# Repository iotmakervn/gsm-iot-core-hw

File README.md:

# Dự án GSM-IOT-CORE

## Mô tả tính năng

## Phần cứng

### Mạch nguyên lý

### Mạch PCB

### 3D
#### Top view

#### Button view

### Film

# Giấy phép

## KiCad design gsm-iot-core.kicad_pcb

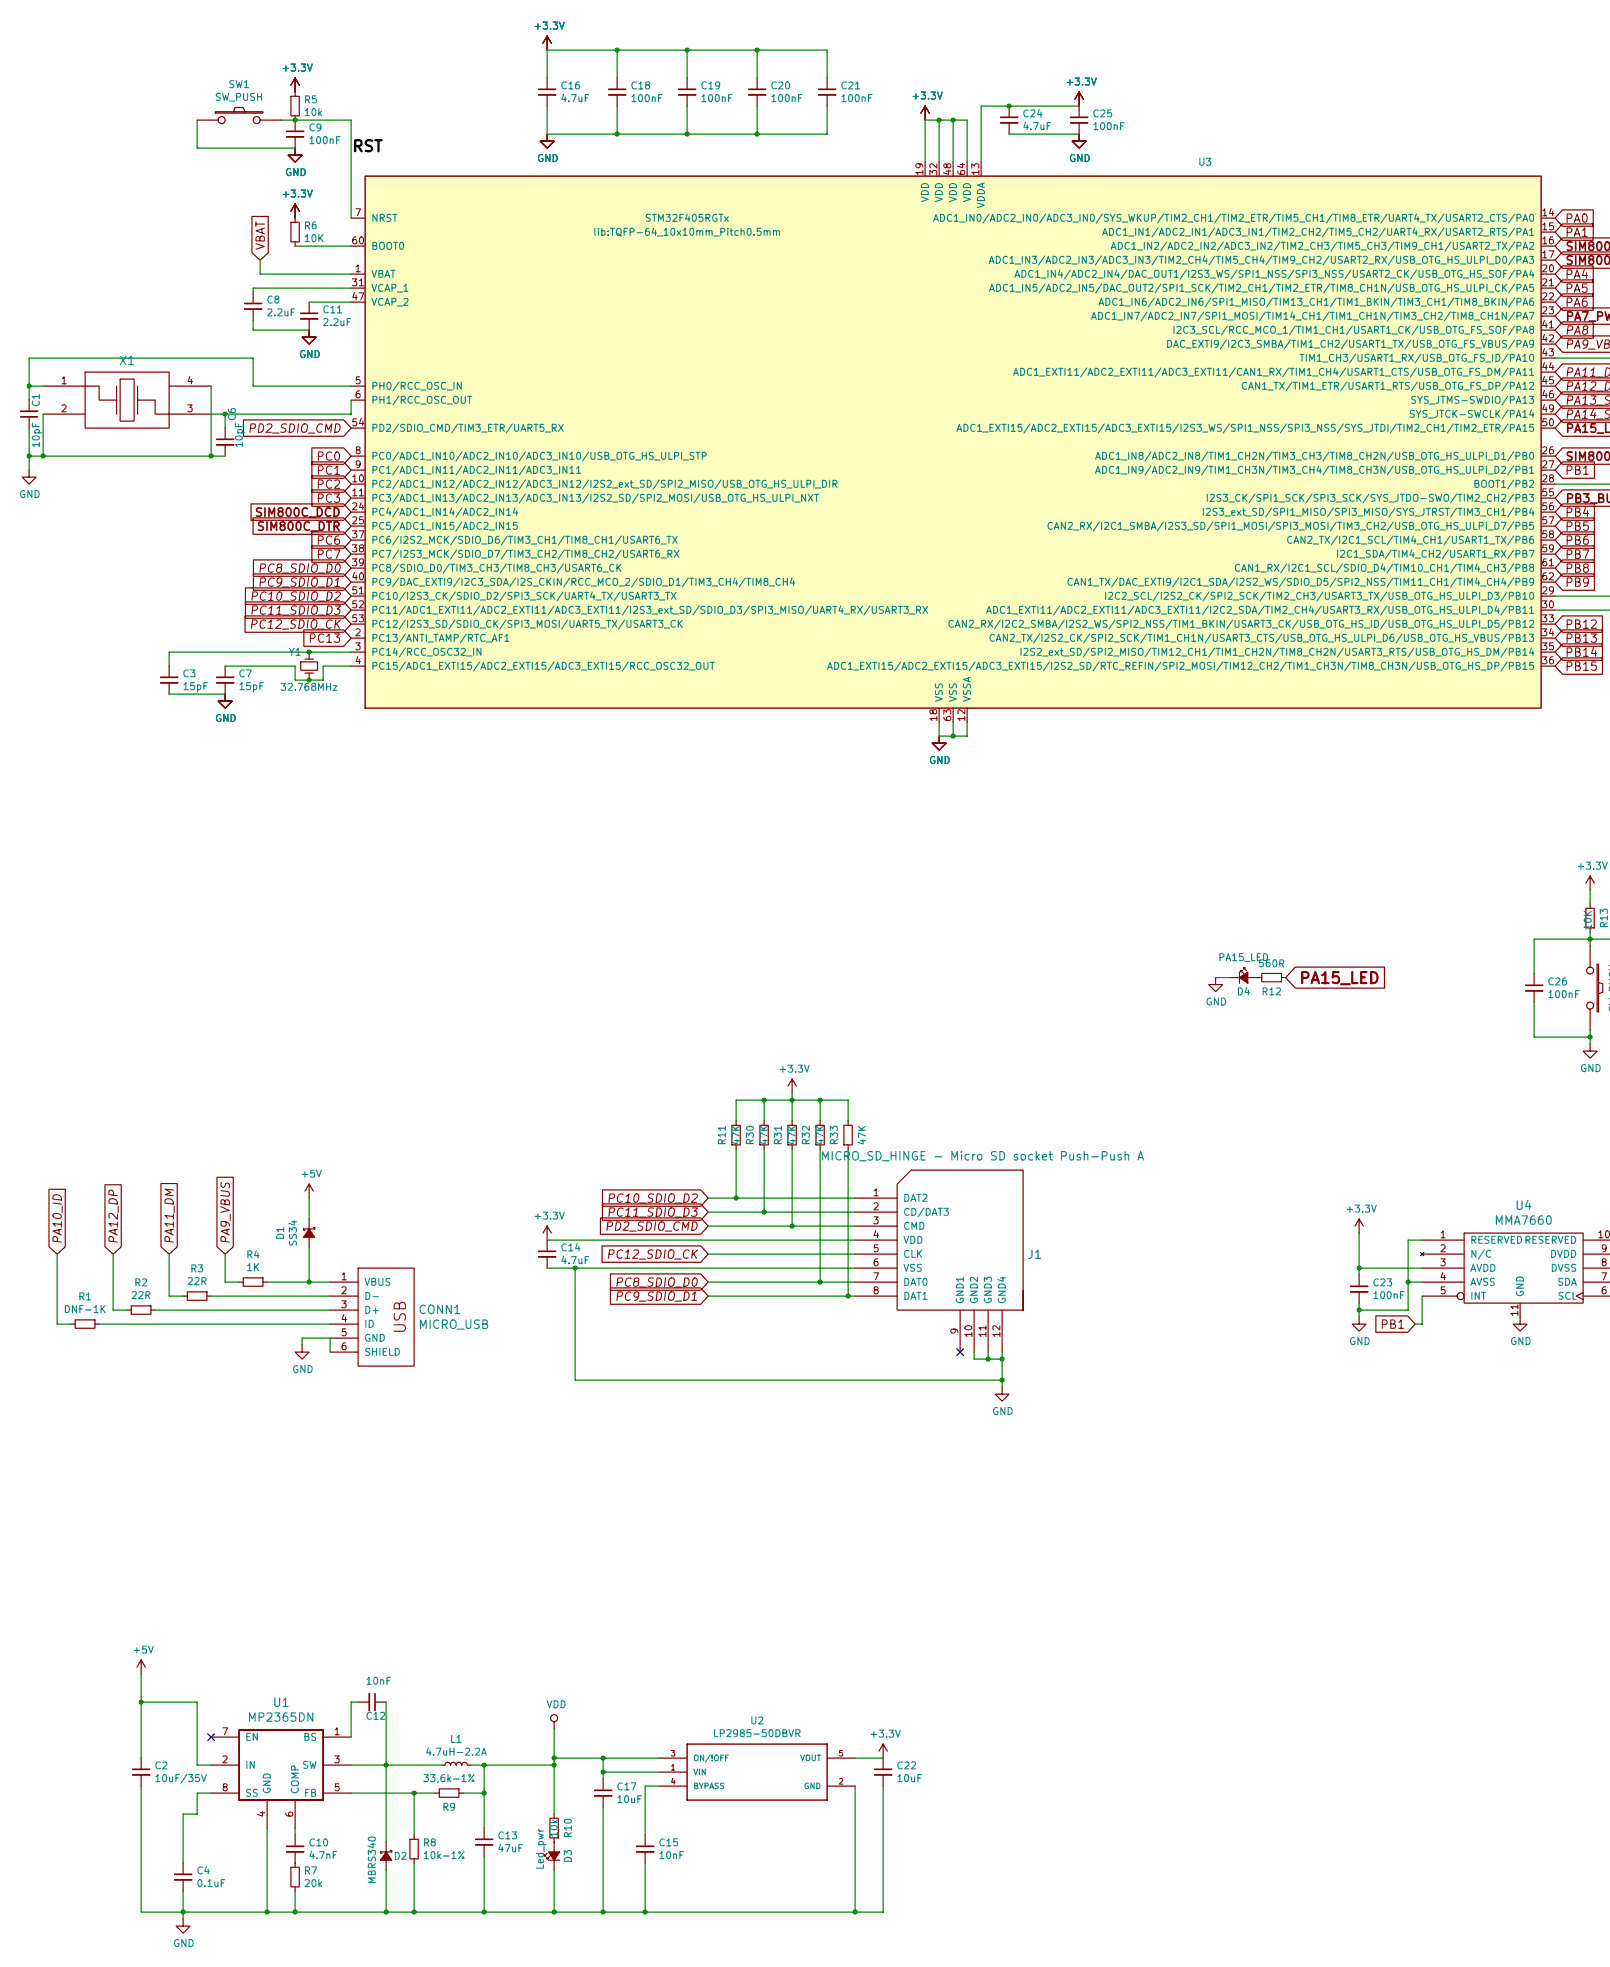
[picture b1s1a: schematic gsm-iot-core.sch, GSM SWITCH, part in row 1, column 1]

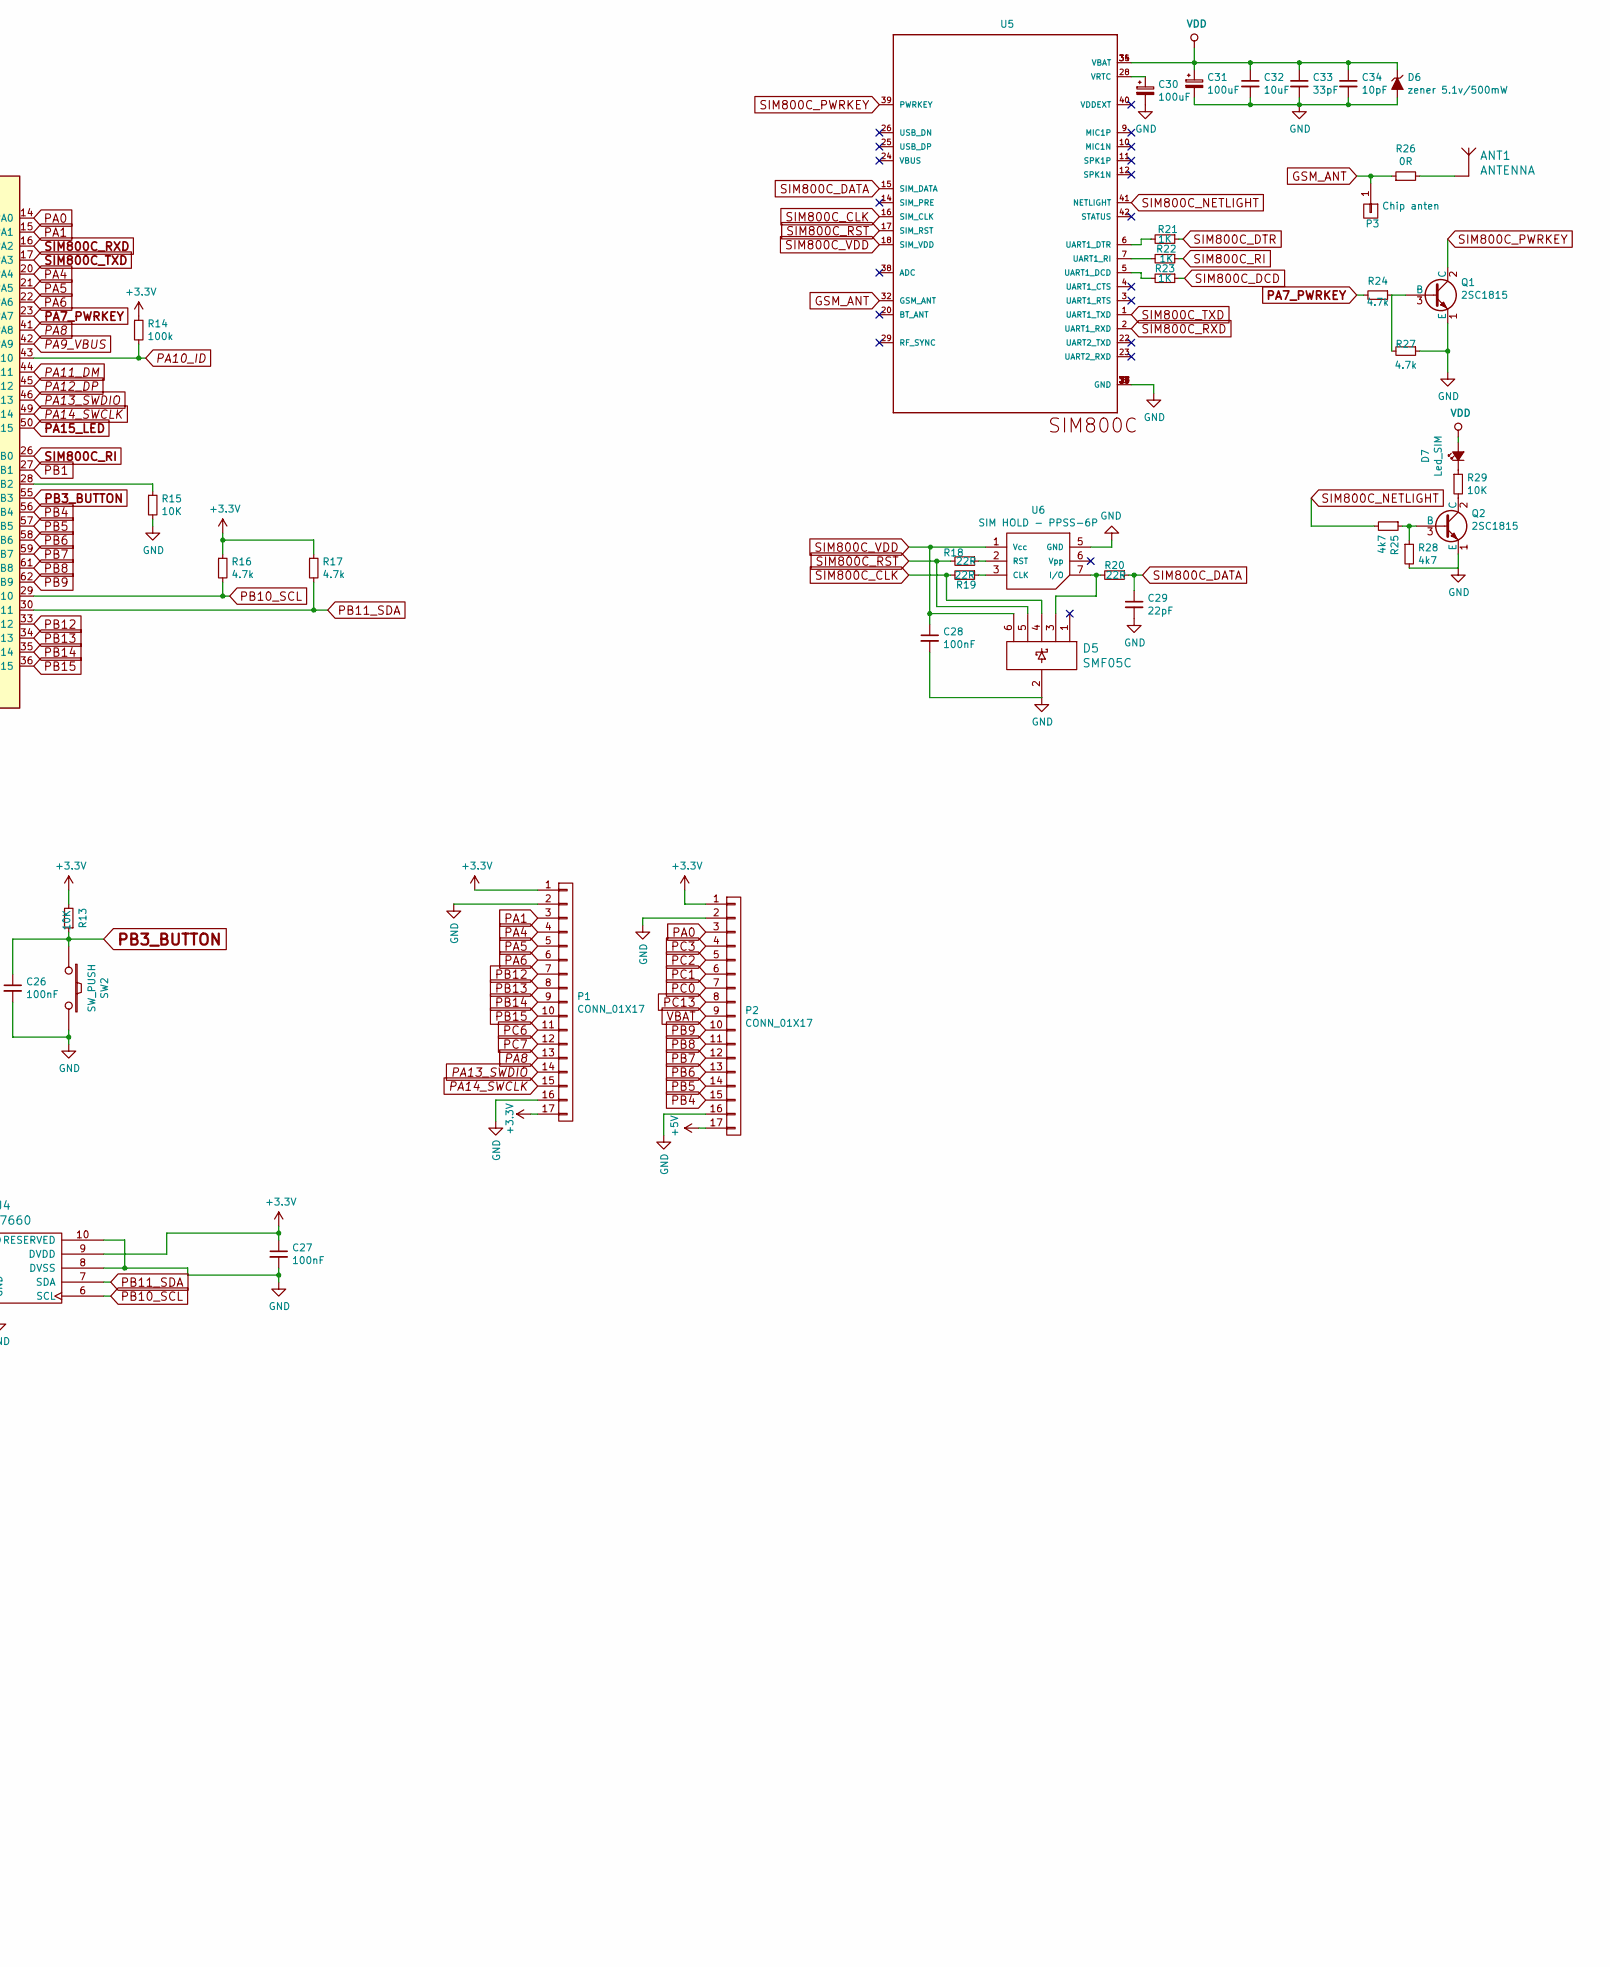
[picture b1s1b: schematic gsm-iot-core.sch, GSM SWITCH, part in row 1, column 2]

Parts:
ANT1: ANTENNA; coaxial_u.fl-r-smt-1
C1, C6, C34: 10pF; C_0603
C2: 10uF/35V; C_1210
C3, C7: 15pF; C_0603
C4: 0.1uF; C_0603
C8, C11: 2.2uF; C_0603
C9, C18, C19, C20, C21, C23, C25, C26, C27, C28: 100nF; C_0603
C10: 4.7nF; C_0603
C12, C15: 10nF; C_0603
C13: 47uF; C_0603
C14, C16, C24: 4.7uF; C_0603
C17, C22, C32: 10uF; C_0603
C29: 22pF; C_0603
C30, C31: 100uF; C_1210
C33: 33pF; C_0603
CONN1: MICRO_USB; Micro_usb_B_smd
D1: SS34; do214ac
D2: MBRS340; do214ab
D3: Led_pwr; LED_0805
D4: PA15_LED; LED_0805
D5: SMF05C; SC-70-6
D6: zener 5.1v/500mW; SOD-123
D7: Led_SIM; LED_0805
J1: MICRO_SD_HINGE - Micro SD socket Push-Push A; MicroSD_Push-Push-A
L1: 4.7uH-2.2A; Choke_SMD_6.3x6.3_H3
P1, P2: CONN_01X17; Pin_Header_Straight_1x17
P3: Chip anten; point_test
Q1, Q2: 2SC1815; SOT-23
R1: DNF-1K; R_0603
R2, R3, R18, R19, R20: 22R; R_0603
R4, R21, R22, R23: 1K; R_0603
R5, R10: 10k; R_0603
R6, R13, R15, R29: 10K; R_0603
R7: 20k; R_0603
R8: 10k-1%; R_0603
R9: 33,6k-1%; R_0603
R11, R30, R31, R32, R33: 47K; R_0603
R12: 560R; R_0603
R14: 100k; R_0603
R16, R17, R24, R27: 4.7k; R_0603
R25, R28: 4k7; R_0603
R26: 0R; R_0603
SW1, SW2: SW_PUSH; SW_SPST_B3U-1000P-B
U1: MP2365DN; SOIC-8-N
U2: LP2985-50DBVR; SOT-23-5
U3: STM32F405RGTx; TQFP-64_10x10mm_Pitch0.5mm
U4: MMA7660; DFN-10-1EP_3x3mm_Pitch0.5mm
U5: SIM800C
U6: SIM HOLD - PPSS-6P; 115I-AEAA
X1: CRYSTAL-24M; Crystal_SMD_5032_4Pads
Y1: 32.768MHz; crystal_smd_32.768_2Pin

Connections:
+3V3: C14.1, C16.1, C18.1, C19.1, C20.1, C21.1, C22.1, C23.1, C24.1, C25.1, C27.1, J1.4 (VDD), P1.1, P1.17, P2.1, R5.1, R6.1, R11.2, R13.2, R14.1, R16.1, R17.1, R30.2, R31.2, R32.2, R33.2, U2.5 (VOUT), U3.13 (VDDA), U3.19 (VDD), U3.32 (VDD), U3.48 (VDD), U3.64 (VDD), U4.3 (AVDD), U4.9 (DVDD)
+5V: C2.1, D1.1 (K), P2.17, U1.2 (IN)
/RST: C9.1, R5.2, SW1.2, U3.7 (NRST)
GND: C1.1, C2.2, C3.2, C4.2, C6.2, C7.2, C8.2, C9.2, C11.2, C13.2, C14.2, C15.2, C16.2, C17.2, C18.2, C19.2, C20.2, C21.2, C22.2, C23.2, C24.2, C25.2, C26.2, C27.2, C28.2, C29.2, C30.2, C31.2, C32.2, C33.2, C34.2, CONN1.5 (GND), CONN1.6 (SHIELD), D2.2 (A), D3.1 (K), D4.1 (K), D5.2, D6.2 (A), J1.6 (VSS), J1.10 (GND2), J1.11 (GND3), J1.12 (GND4), P1.2, P1.16, P2.2, P2.16, Q1.1 (E), Q2.1 (E), R7.2, R8.2, R15.2, R27.1, R28.2, SW1.1, SW2.2, U1.4 (GND), U2.2 (GND), U3.12 (VSSA), U3.18 (VSS), U3.63 (VSS), U4.1 (RESERVED), U4.4 (AVSS), U4.8 (DVSS), U4.10 (RESERVED), U4.11 (GND), U5.8 (GND), U5.13 (GND), U5.19 (GND), U5.21 (GND), U5.27 (GND), U5.30 (GND), U5.31 (GND), U5.33 (GND), U5.36 (GND), U5.37 (GND), U6.5 (GND), X1.2, X1.4
GSM_ANT: P3.1, R26.1, U5.32 (GSM_ANT)
unnamed: ANT1.1, R26.2
unnamed: C1.2, U3.5 (PH0/RCC_OSC_IN), X1.1
unnamed: C3.1, U3.3 (PC14/RCC_OSC32_IN), Y1.1
unnamed: C4.1, U1.8 (SS)
unnamed: C6.1, U3.6 (PH1/RCC_OSC_OUT), X1.3
unnamed: C7.1, U3.4 (PC15/ADC1_EXTI15/ADC2_EXTI15/ADC3_EXTI1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), Y1.2
unnamed: C8.1, U3.31 (VCAP_1)
unnamed: C10.1, U1.6 (COMP)
unnamed: C10.2, R7.1
unnamed: C11.1, U3.47 (VCAP_2)
unnamed: C12.1, D2.1 (K), L1.1, U1.3 (SW)
unnamed: C12.2, U1.1 (BS)
unnamed: C15.1, U2.4 (BYPASS)
unnamed: C28.1, D5.6
unnamed: C30.1, U5.28 (VRTC)
unnamed: CONN1.1 (VBUS), D1.2 (A), R4.1
unnamed: CONN1.2 (D-), R3.1
unnamed: CONN1.3 (D+), R2.1
unnamed: CONN1.4 (ID), R1.1
unnamed: D3.2 (A), R10.1
unnamed: D4.2 (A), R12.2
unnamed: D5.3, R20.2, U6.7 (I/O)
unnamed: D7.1 (K), R29.1
unnamed: Q1.3 (B), R24.1, R27.2
unnamed: Q2.2 (C), R29.2
unnamed: Q2.3 (B), R25.1, R28.1
unnamed: R6.2, U3.60 (BOOT0)
unnamed: R8.1, R9.2, U1.5 (FB)
unnamed: R15.1, U3.28 (BOOT1/PB2)
unnamed: R18.1, U6.2 (RST)
unnamed: R19.1, U6.3 (CLK)
unnamed: R21.2, U5.6 (UART1_DTR)
unnamed: R22.2, U5.7 (UART1_RI)
unnamed: R23.2, U5.5 (UART1_DCD)
PA0: P2.3, U3.14 (ADC1_IN0/ADC2_IN0/ADC3_IN0/SYS_WKUP/TIM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)
PA1: P1.3, U3.15 (ADC1_IN1/ADC2_IN1/ADC3_IN1/TIM2_CH2/TIM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)
PA4: P1.4, U3.20 (ADC1_IN4/ADC2_IN4/DAC_OUT1/I2S3_WS/SPI1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)
PA5: P1.5, U3.21 (ADC1_IN5/ADC2_IN5/DAC_OUT2/SPI1_SCK/TIM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)
PA6: P1.6, U3.22 (ADC1_IN6/ADC2_IN6/SPI1_MISO/TIM13_CH1/T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)
PA7_PWRKEY: R24.2, U3.23 (ADC1_IN7/ADC2_IN7/SPI1_MOSI/TIM14_CH1/T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)
PA8: P1.13, U3.41 (I2C3_SCL/RCC_MCO_1/TIM1_CH1/USART1_CK/U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)
PA9_VBUS: R4.2, U3.42 (DAC_EXTI9/I2C3_SMBA/TIM1_CH2/USART1_TX/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)
PA10_ID: R1.2, R14.2, U3.43 (TIM1_CH3/USART1_RX/USB_OTG_FS_ID/PA10)
PA11_DM: R3.2, U3.44 (ADC1_EXTI11/ADC2_EXTI11/ADC3_EXTI11/CAN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)
PA12_DP: R2.2, U3.45 (CAN1_TX/TIM1_ETR/USART1_RTS/USB_OTG_FS_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)
PA13_SWDIO: P1.14, U3.46 (SYS_JTMS-SWDIO/PA13)
PA14_SWCLK: P1.15, U3.49 (SYS_JTCK-SWCLK/PA14)
PA15_LED: R12.1, U3.50 (ADC1_EXTI15/ADC2_EXTI15/ADC3_EXTI15/I2S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)
PB1: U3.27 (ADC1_IN9/ADC2_IN9/TIM1_CH3N/TIM3_CH4/TI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), U4.5 (INT)
PB3_BUTTON: C26.1, R13.1, SW2.1, U3.55 (I2S3_CK/SPI1_SCK/SPI3_SCK/SYS_JTDO-SWO/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)
PB4: P2.15, U3.56 (I2S3_ext_SD/SPI1_MISO/SPI3_MISO/SYS_JTR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)
PB5: P2.14, U3.57 (CAN2_RX/I2C1_SMBA/I2S3_SD/SPI1_MOSI/SPI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)
PB6: P2.13, U3.58 (CAN2_TX/I2C1_SCL/TIM4_CH1/USART1_TX/PB6)
PB7: P2.12, U3.59 (I2C1_SDA/TIM4_CH2/USART1_RX/PB7)
PB8: P2.11, U3.61 (CAN1_RX/I2C1_SCL/SDIO_D4/TIM10_CH1/TIM4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)
PB9: P2.10, U3.62 (CAN1_TX/DAC_EXTI9/I2C1_SDA/I2S2_WS/SDIO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)
PB10_SCL: R16.2, U3.29 (I2C2_SCL/I2S2_CK/SPI2_SCK/TIM2_CH3/USAR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), U4.6 (SCL)
PB11_SDA: R17.2, U3.30 (ADC1_EXTI11/ADC2_EXTI11/ADC3_EXTI11/I2C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), U4.7 (SDA)
PB12: P1.7, U3.33 (CAN2_RX/I2C2_SMBA/I2S2_WS/SPI2_NSS/TIM1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)
PB13: P1.8, U3.34 (CAN2_TX/I2S2_CK/SPI2_SCK/TIM1_CH1N/USAR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)
PB14: P1.9, U3.35 (I2S2_ext_SD/SPI2_MISO/TIM12_CH1/TIM1_CH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)
PB15: P1.10, U3.36 (ADC1_EXTI15/ADC2_EXTI15/ADC3_EXTI15/I2S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)
PC0: P2.7, U3.8 (PC0/ADC1_IN10/ADC2_IN10/ADC3_IN10/USB_O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)
PC1: P2.6, U3.9 (PC1/ADC1_IN11/ADC2_IN11/ADC3_IN11)
PC2: P2.5, U3.10 (PC2/ADC1_IN12/ADC2_IN12/ADC3_IN12/I2S2_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)
PC3: P2.4, U3.11 (PC3/ADC1_IN13/ADC2_IN13/ADC3_IN13/I2S2_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)
PC6: P1.11, U3.37 (PC6/I2S2_MCK/SDIO_D6/TIM3_CH1/TIM8_CH1/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)
PC7: P1.12, U3.38 (PC7/I2S3_MCK/SDIO_D7/TIM3_CH2/TIM8_CH2/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)
PC8_SDIO_D0: J1.7 (DAT0), R32.1, U3.39 (PC8/SDIO_D0/TIM3_CH3/TIM8_CH3/USART6_CK)
PC9_SDIO_D1: J1.8 (DAT1), R33.1, U3.40 (PC9/DAC_EXTI9/I2C3_SDA/I2S_CKIN/RCC_MCO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)
PC10_SDIO_D2: J1.1 (DAT2), R11.1, U3.51 (PC10/I2S3_CK/SDIO_D2/SPI3_SCK/UART4_TX/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)
PC11_SDIO_D3: J1.2 (CD/DAT3), R30.1, U3.52 (PC11/ADC1_EXTI11/ADC2_EXTI11/ADC3_EXTI1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)
PC12_SDIO_CK: J1.5 (CLK), U3.53 (PC12/I2S3_SD/SDIO_CK/SPI3_MOSI/UART5_TX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)
PC13: P2.8, U3.2 (PC13/ANTI_TAMP/RTC_AF1)
PD2_SDIO_CMD: J1.3 (CMD), R31.1, U3.54 (PD2/SDIO_CMD/TIM3_ETR/UART5_RX)
SIM800C_CLK: D5.4, R19.2, U5.16 (SIM_CLK)
SIM800C_DATA: C29.1, R20.1, U5.15 (SIM_DATA)
SIM800C_DCD: R23.1, U3.24 (PC4/ADC1_IN14/ADC2_IN14)
SIM800C_DTR: R21.1, U3.25 (PC5/ADC1_IN15/ADC2_IN15)
SIM800C_NETLIGHT: R25.2, U5.41 (NETLIGHT)
SIM800C_PWRKEY: Q1.2 (C), U5.39 (PWRKEY)
SIM800C_RI: R22.1, U3.26 (ADC1_IN8/ADC2_IN8/TIM1_CH2N/TIM3_CH3/TI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)
SIM800C_RST: D5.5, R18.2, U5.17 (SIM_RST)
SIM800C_RXD: U3.16 (ADC1_IN2/ADC2_IN2/ADC3_IN2/TIM2_CH3/TIM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), U5.2 (UART1_RXD)
SIM800C_TXD: U3.17 (ADC1_IN3/ADC2_IN3/ADC3_IN3/TIM2_CH4/TIM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), U5.1 (UART1_TXD)
SIM800C_VDD: U5.18 (SIM_VDD), U6.1 (Vcc)
VBAT: P2.9, U3.1 (VBAT)
VDD: C13.1, C17.1, C31.1, C32.1, C33.1, C34.1, D6.1 (K), D7.2 (A), L1.2, R9.1, R10.2, U2.1 (VIN), U2.3 (ON/!OFF), U5.34 (VBAT), U5.35 (VBAT)

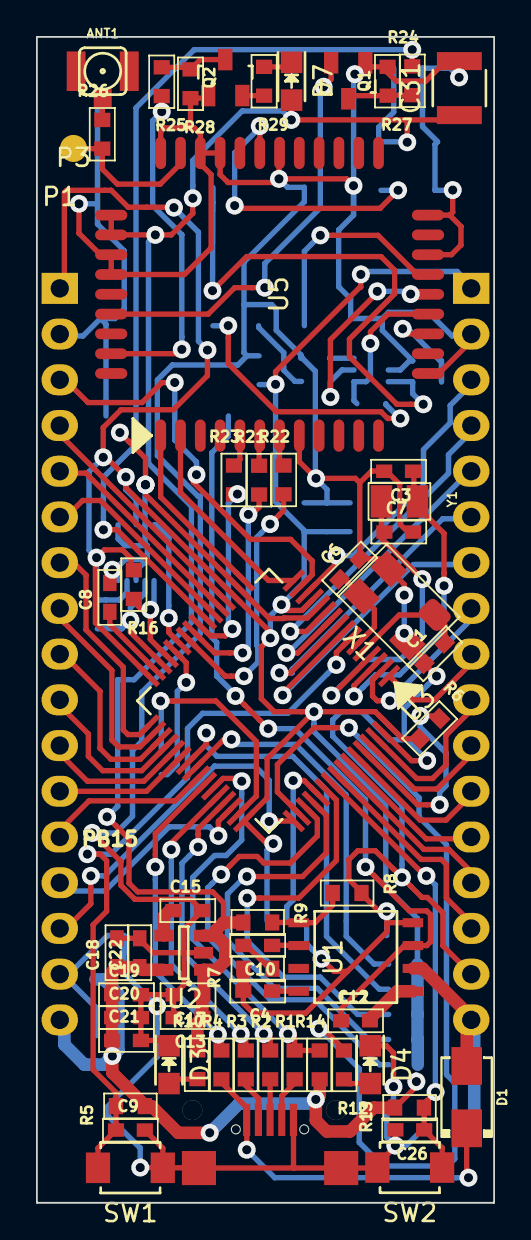
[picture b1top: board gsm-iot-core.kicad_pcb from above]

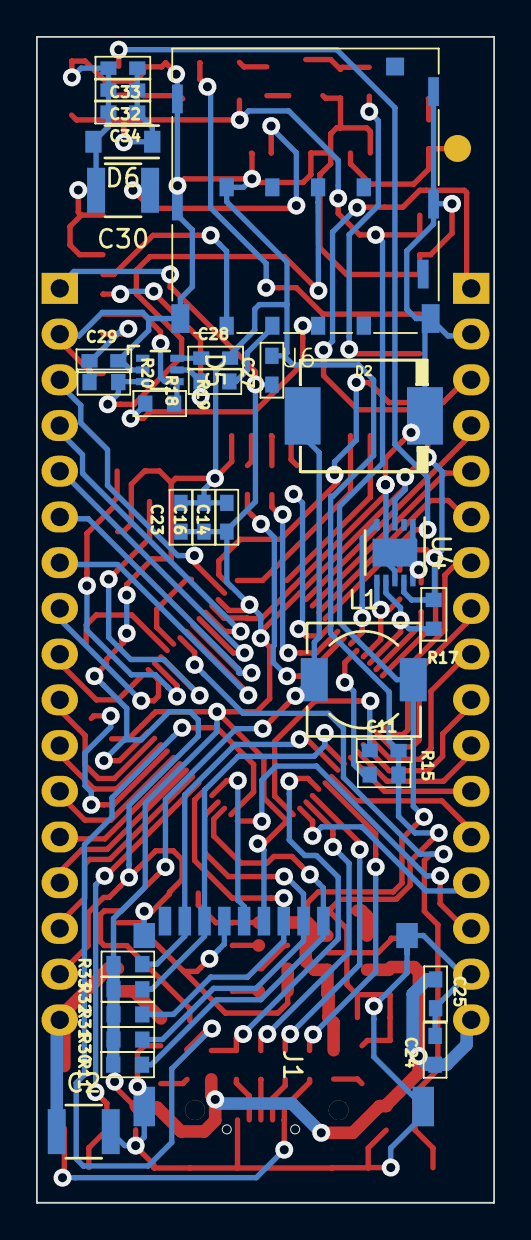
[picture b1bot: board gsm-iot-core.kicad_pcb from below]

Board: 2 copper layers, 25.4 x 64.8 mm, 92 parts (31 on the bottom side), 93 nets.

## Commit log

2016-08-12 add REAMDE file
2016-08-12 Create project, but need to check connect between STM32 & SIM800C
2016-09-06 mistake
2016-09-06 add .gitignore
2016-09-15 branch upstream
2016-09-15 Error add footprint-not updata footprint, local of component is bad
2016-09-15 add assets file and fix README
2016-09-15 fix mistake README
2016-09-15 fix README
2016-09-15 fix README file
2016-09-15 Fix error invalid foortprint- a error footprint file, add new footprint for component
2016-09-16 new PCB
2016-09-26 fix 3th
2016-09-28 PCB new
2016-09-28 Fix mistake
2016-09-29 Branch LONGER
2016-09-29 add picture 3D
2016-09-30 Fails
2016-10-02 fix PCB
2016-10-03 Fail
2016-10-06 Fix power part of schematic & footprint crystal
2016-10-07 Modify microSD diagram & connect betwenn MMA7660 and STM
2016-10-07 Modify length board 9x2,7 (in)
2016-10-08 setup component
2016-10-11 all connect usb & SD card well
2016-10-20 completed connect tracks
2016-10-23 fix 1/3 via & track distance
2016-10-24 Final pcb
